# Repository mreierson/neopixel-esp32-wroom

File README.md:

## NeoPixel + ESP32 Controller  

ESP32-based board with level-converter to control a NeoPixel strip  
Firmware available at https://github.com/mreierson/neopixel-esp32-firmware

WROOM WROOM!

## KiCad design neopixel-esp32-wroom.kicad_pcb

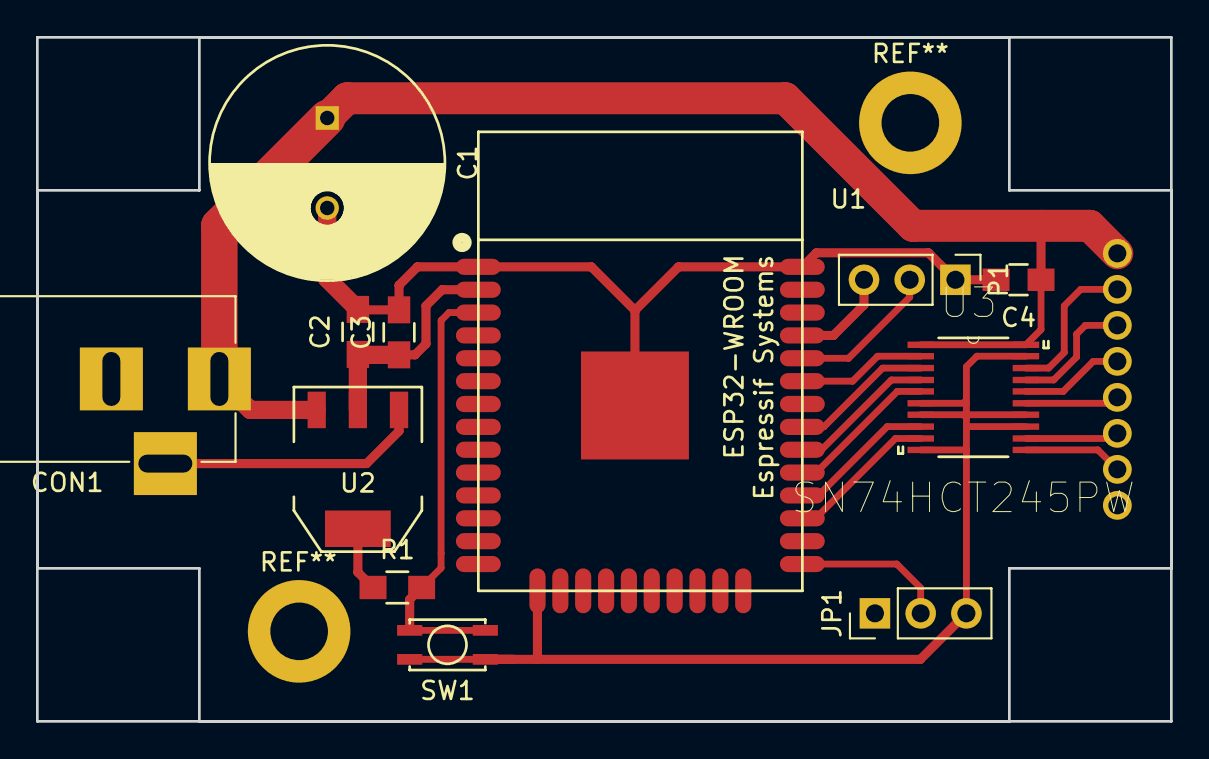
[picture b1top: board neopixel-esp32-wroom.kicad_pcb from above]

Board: 2 copper layers, 63.0 x 38.0 mm, 13 parts (1 on the bottom side), 19 nets.

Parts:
C1: CP; C_Radial_D13_L25_P5
C2, C3: 2.2uf; C_0805_HandSoldering
C4: CP; C_0805_HandSoldering
CON1: BARREL_JACK
CON2: EN3P8MRAPCBN
JP1: JUMPER3; Pin_Header_Straight_1x03_Pitch2.54mm
P1: CONN_01X03; Pin_Header_Straight_1x03_Pitch2.54mm
R1: R; R_0805_HandSoldering
SW1: SW_PUSH; KMR231GLFS
U1: ESP32-WROOM
U2: LM1117-3.3; SOT-223
U3: SN74HCT245PW; SOP65P640X120-20N

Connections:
+3V3: C2.1, C3.1, R1.1, U1.2, U2.2
+5V: C1.1, C4.1, CON1.1, CON2.5, U2.3, U3.1, U3.20
EN_IN: R1.2, SW1.2, U1.3
ESP_IO1: U1.33, U3.2
ESP_IO2: U1.31, U3.3
ESP_IO3: U1.30, U3.4
ESP_IO4: U1.29, U3.5
ESP_IO5: U1.28, U3.8
ESP_IO6: U1.27, U3.9
GND: C1.2, C2.2, C3.2, C4.2, CON1.2, CON1.3, CON2.4, JP1.3, P1.1, SW1.1, U1.1, U1.15, U1.38, U1.39, U2.1, U3.6, U3.7, U3.10, U3.13, U3.14, U3.19
NEO_IO1: CON2.6, U3.18
NEO_IO2: CON2.7, U3.17
NEO_IO3: CON2.8, U3.16
NEO_IO4: CON2.1, U3.15
NEO_IO5: CON2.2, U3.12
NEO_IO6: CON2.3, U3.11
unnamed: JP1.2, U1.25
RXD: P1.2, U1.34
TXD: P1.3, U1.35
